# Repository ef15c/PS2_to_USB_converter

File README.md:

# PS2_to_USB_converter

 This board allow to plug PS/2 devices (keyboards or mice) to a computer using a standard USB connector.

- Uses a low cost STM32F103 "bluepill"
- Two independent PS/2 ports
- Each port can be connected to a mouse, a keyboard or left unconnected. The connected devices are automatically presented to the host computer
- Automatic recognition of the type of the PS/2 device : you can connect any keyboard or mouse on each of the PS/2 connector of the board
- No specific driver required on host computer
- Hardware and Firmware source code provided
- 2 LEDs per port for PS/2 device type identification and traffic information

Directories:
- din2usb_adapter contains the KICAD files of the board.
- stm103_ps2_to_usb contains the firmware.

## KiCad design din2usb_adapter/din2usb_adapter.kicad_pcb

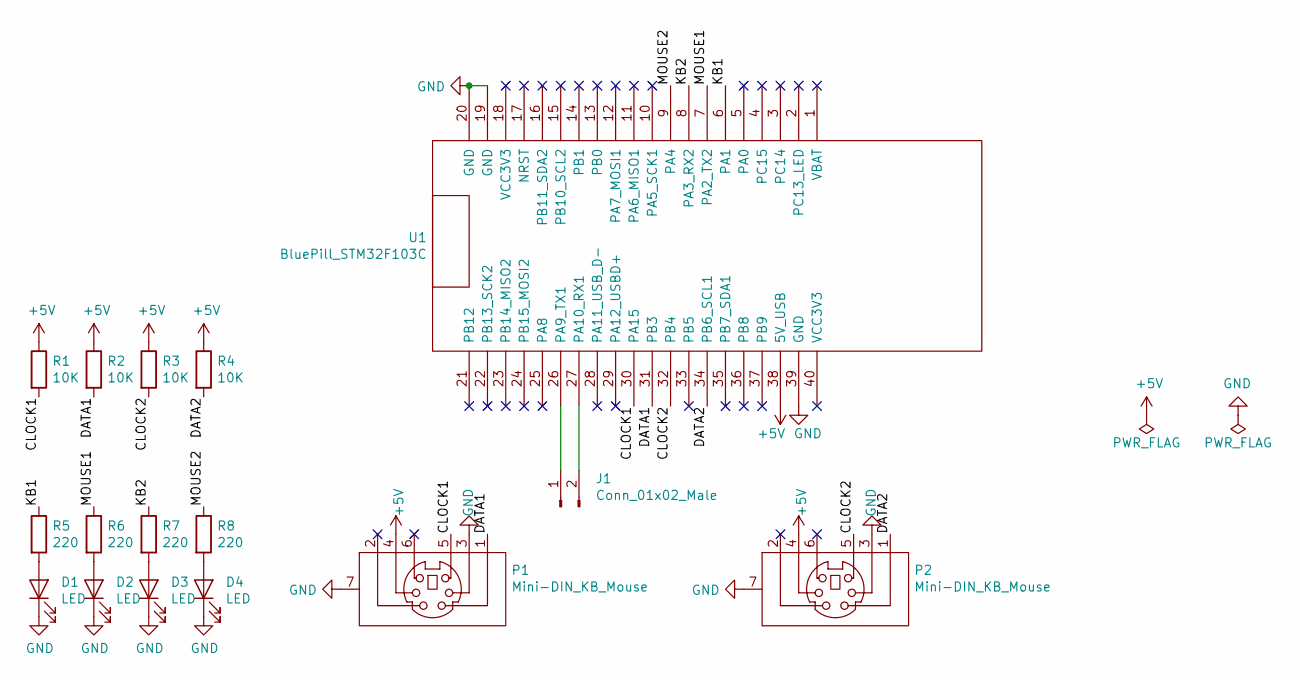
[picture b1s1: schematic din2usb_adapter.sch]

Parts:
D1, D2, D3, D4: LED; LED_D3.0mm
J1: Conn_01x02_Male; PinHeader_1x02_P2.54mm_Vertical_TX_RX
P1, P2: Mini-DIN_KB_Mouse; Connector_Mini-DIN_Female_6Pin_2rows
R1, R2, R3, R4: 10K; R_Axial_DIN0207_L6.3mm_D2.5mm_P10.16mm_Horizontal
R5, R6, R7, R8: 220; R_Axial_DIN0207_L6.3mm_D2.5mm_P10.16mm_Horizontal
U1: BluePill_STM32F103C; BluePill_STM32F103C_without_pgm_pins

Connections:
+5V: P1.4, P2.4, R1.1, R2.1, R3.1, R4.1, U1.38 (5V_USB)
/CLOCK1: P1.5, R1.2, U1.30 (PA15)
/CLOCK2: P2.5, R3.2, U1.32 (PB4)
/DATA1: P1.1, R2.2, U1.31 (PB3)
/DATA2: P2.1, R4.2, U1.34 (PB6_SCL1)
/KB1: R5.1, U1.6 (PA1)
/KB2: R7.1, U1.8 (PA3_RX2)
/MOUSE1: R6.1, U1.7 (PA2_TX2)
/MOUSE2: R8.1, U1.9 (PA4)
GND: D1.1 (K), D2.1 (K), D3.1 (K), D4.1 (K), P1.3, P1.7 (Shell), P2.3, P2.7 (Shell), U1.19 (GND), U1.20 (GND), U1.39 (GND)
unnamed: D1.2 (A), R5.2
unnamed: D2.2 (A), R6.2
unnamed: D3.2 (A), R7.2
unnamed: D4.2 (A), R8.2
unnamed: J1.1, U1.26 (PA9_TX1)
unnamed: J1.2, U1.27 (PA10_RX1)

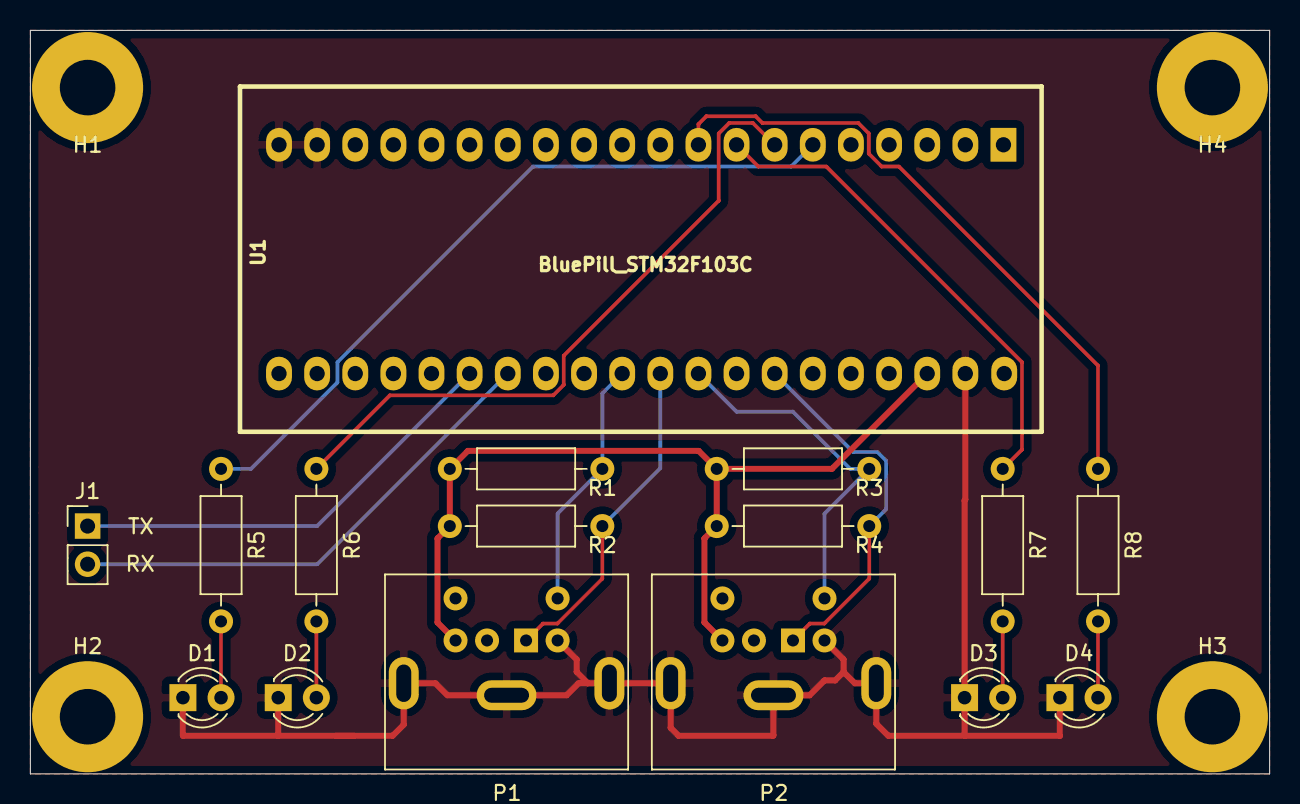
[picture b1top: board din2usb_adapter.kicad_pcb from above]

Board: 4 copper layers, 82.5 x 49.5 mm, 20 parts (0 on the bottom side), 16 nets.

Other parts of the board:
H1, H2, H3, H4: MountingHole_3.7mm_Pad

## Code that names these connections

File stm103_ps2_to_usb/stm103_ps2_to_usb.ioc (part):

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Mcu.Name=STM32F103C(8-B)Tx
Mcu.Package=LQFP48
Mcu.UserName=STM32F103C8Tx
PA1.GPIOParameters=GPIO_Label
PA1.GPIO_Label=KB1
PA1.Signal=GPIO_Output
PA11.Mode=Device
PA11.Signal=USB_DM
PA12.Mode=Device
PA12.Signal=USB_DP
PA13.Mode=Serial_Wire
PA13.Signal=SYS_JTMS-SWDIO
PA14.Mode=Serial_Wire
PA14.Signal=SYS_JTCK-SWCLK
PA15.GPIOParameters=GPIO_Label,GPIO_ModeDefaultEXTI
PA15.GPIO_Label=CLOCK1
PA15.GPIO_ModeDefaultEXTI=GPIO_MODE_IT_RISING_FALLING
PA15.Signal=GPXTI15
PA2.GPIOParameters=GPIO_Label
PA2.GPIO_Label=MOUSE1
PA2.Signal=GPIO_Output
PA3.GPIOParameters=GPIO_Label
PA3.GPIO_Label=KB2
PA3.Signal=GPIO_Output
PA4.GPIOParameters=GPIO_Label
PA4.GPIO_Label=MOUSE2
PA4.Signal=GPIO_Output
PB3.GPIOParameters=GPIO_Label
PB3.GPIO_Label=DATA1
PB3.Signal=GPIO_Input
PB4.GPIOParameters=GPIO_Label,GPIO_ModeDefaultEXTI
PB4.GPIO_Label=CLOCK2
PB4.GPIO_ModeDefaultEXTI=GPIO_MODE_IT_RISING_FALLING
PB4.Signal=GPXTI4
PB6.GPIOParameters=GPIO_Label
PB6.GPIO_Label=DATA2
PB6.Signal=GPIO_Input
PC13-TAMPER-RTC.GPIOParameters=GPIO_Label
PC13-TAMPER-RTC.GPIO_Label=ONBOARD_LED
PC13-TAMPER-RTC.Signal=GPIO_Output
PD0-OSC_IN.Mode=HSE-External-Oscillator
PD0-OSC_IN.Signal=RCC_OSC_IN
PD1-OSC_OUT.Mode=HSE-External-Oscillator
PD1-OSC_OUT.Signal=RCC_OSC_OUT
RCC.SYSCLKFreq_VALUE=48000000
RCC.SYSCLKSource=RCC_SYSCLKSOURCE_PLLCLK
board=stm103_template

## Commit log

2021-04-05 Initial delivery of firmware
2021-04-05 KICAP project
2021-04-05 Add board picture
